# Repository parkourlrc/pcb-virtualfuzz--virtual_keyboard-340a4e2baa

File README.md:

# virtual_keyboard

Uses kmk for the firmware, maybe in the future I will switch to Rust.

The goal of this keyboard is to be one that I like, not one with a bunch
of fancy features. It's as minimal as I like it to be, 65% keyboards seem
good, but I still need F keys because for some games it better to have them.

For the arrow keys, I don't think it's that bad not having them thanks to
WASD keys.

## Schematic

## PCB

## Case

The case is supposed to stick together using screws, not sure if they will fit.\
I think I'll use some tape or a wire to hold it together if it doesn't fit.

## Bill of Materials

### Electronics

|QTY|Name|Part number|
|---|----|-----------|
|1|Orpheus PICO|
|81|Diodes|1N4148WL|
|81|Kailh Hotswap Sockets|

### Keyboard components

|QTY|Name|
|---|----|
|1|Bottom case|
|1|Top case|
|4|2mm (Self-drilling?) Screws|
|81|DSA keycaps|
|81|Cherry MX Switches|
|1|6u Stabilizer|
|2|2u Stabilizers|

## Keyboard Layout (KLE raw data)

ISO layout

Resize: Spacebar; Shift key
```
["Esc","F1","F2","F3","F4","F5","F6","F7","F8","F9","F10","F11","F12","Print screen","Delete"],
["#\n@","1\nà","2\né","3\nè","4\nê","5\n(","6\n)","7\n‘","8\n’","9\n«","0\n»","\"\n'","¨\n^",{w:2},"Backspace"],
[{w:1.5},"Tab","A","Z\n£","E\n€","R","T\n{","Y\n}","U","I","O","P","–\n-","±\n+",{x:0.25,w:1.25,h:2,w2:1.5,h2:1,x2:-0.25},"Enter"],
[{w:1.75},"Caps Lock","Q","S","D\n$","F","G","H","J","K","L","M","\\\n/","½\n*"],
[{w:1.25},"Shift",">\n<","W","X","C","V","B","N","?\n.","!\n,","…\n:","=\n;",{w:1.75},"Shift","↑"],
["Ctrl","Fn","Super","Alt",{a:7,w:6},"","Alt Gr","Super","Ctrl","←","↓","→"]
```

## License

[Licensed under the MIT license](LICENSE.md)

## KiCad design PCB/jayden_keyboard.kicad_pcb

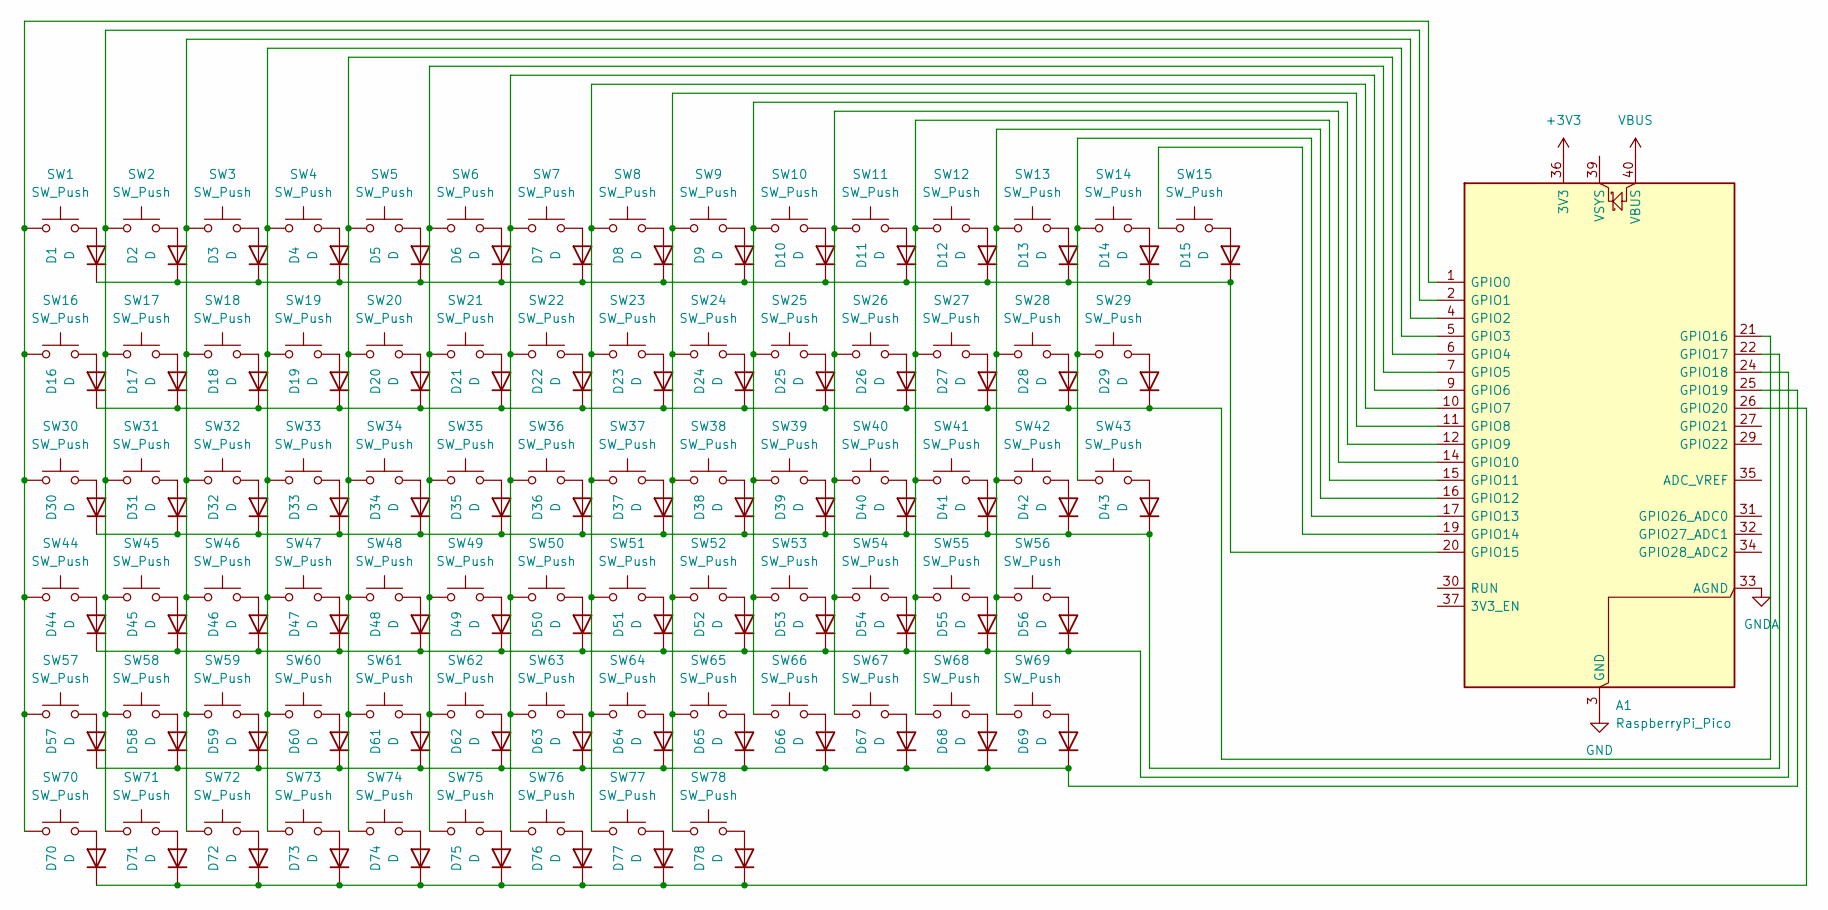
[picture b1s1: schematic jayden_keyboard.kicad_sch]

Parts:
A1: RaspberryPi_Pico; RaspberryPi_Pico_Common_THT_MountingHoles
D1, D2, D3, D4, D5, D6, D7, D8, D9, D10, D11, D12, D13, D14, D15, D16, D17, D18, D19, D20, D21, D22, D23, D24, D25, D26, D27, D28, D29, D30, D31, D32, D33, D34, D35, D36, D37, D38, D39, D40, D41, D42, D43, D44, D45, D46, D47, D48, D49, D50, D51, D52, D53, D54, D55, D56, D57, D58, D59, D60, D61, D62, D63, D64, D65, D66, D67, D68, D69, D70, D71, D72, D73, D74, D75, D76, D77, D78: D; D_DO-35_SOD27_P7.62mm_Horizontal
SW1, SW2, SW3, SW4, SW5, SW6, SW7, SW8, SW9, SW10, SW11, SW12, SW13, SW14, SW15, SW16, SW17, SW18, SW19, SW20, SW21, SW22, SW23, SW24, SW25, SW26, SW27, SW28, SW31, SW32, SW33, SW34, SW35, SW36, SW37, SW38, SW39, SW40, SW41, SW42, SW45, SW46, SW47, SW48, SW49, SW50, SW51, SW52, SW53, SW54, SW55, SW56, SW58, SW59, SW60, SW61, SW62, SW63, SW64, SW65, SW66, SW67, SW68, SW71, SW72, SW73, SW76, SW77: SW_Push; MX-Hotswap-1U
SW29: SW_Push; MX-Hotswap-2U
SW30: SW_Push; MX-Hotswap-1.5U
SW43: SW_Push; MX-Hotswap-ISO
SW44: SW_Push; MX-Hotswap-1.75U
SW57, SW70, SW75, SW78: SW_Push; MX-Hotswap-1.25U
SW69: SW_Push; MX-Hotswap-2.75U
SW74: SW_Push; MX-Hotswap-6.25U

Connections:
+3V3: A1.36 (3V3)
GND: A1.3 (GND), A1.8 (GND), A1.13 (GND), A1.18 (GND), A1.23 (GND), A1.28 (GND), A1.38 (GND)
GNDA: A1.33 (AGND)
unnamed: A1.1 (GPIO0), SW1.1, SW16.1, SW30.1, SW44.1, SW57.1, SW70.1
unnamed: A1.2 (GPIO1), SW2.1, SW17.1, SW31.1, SW45.1, SW58.1, SW71.1
unnamed: A1.4 (GPIO2), SW3.1, SW18.1, SW32.1, SW46.1, SW59.1, SW72.1
unnamed: A1.5 (GPIO3), SW4.1, SW19.1, SW33.1, SW47.1, SW60.1, SW73.1
unnamed: A1.6 (GPIO4), SW5.1, SW20.1, SW34.1, SW48.1, SW61.1, SW74.1
unnamed: A1.7 (GPIO5), SW6.1, SW21.1, SW35.1, SW49.1, SW62.1, SW75.1
unnamed: A1.9 (GPIO6), SW7.1, SW22.1, SW36.1, SW50.1, SW63.1, SW76.1
unnamed: A1.10 (GPIO7), SW8.1, SW23.1, SW37.1, SW51.1, SW64.1, SW77.1
unnamed: A1.11 (GPIO8), SW9.1, SW24.1, SW38.1, SW52.1, SW65.1, SW78.1
unnamed: A1.12 (GPIO9), SW10.1, SW25.1, SW39.1, SW53.1, SW66.1
unnamed: A1.14 (GPIO10), SW11.1, SW26.1, SW40.1, SW54.1, SW67.1
unnamed: A1.15 (GPIO11), SW12.1, SW27.1, SW41.1, SW55.1, SW68.1
unnamed: A1.16 (GPIO12), SW13.1, SW28.1, SW42.1, SW56.1, SW69.1
unnamed: A1.17 (GPIO13), SW14.1, SW29.1, SW43.1
unnamed: A1.19 (GPIO14), SW15.1
unnamed: A1.20 (GPIO15), D1.1 (K), D2.1 (K), D3.1 (K), D4.1 (K), D5.1 (K), D6.1 (K), D7.1 (K), D8.1 (K), D9.1 (K), D10.1 (K), D11.1 (K), D12.1 (K), D13.1 (K), D14.1 (K), D15.1 (K)
unnamed: A1.21 (GPIO16), D16.1 (K), D17.1 (K), D18.1 (K), D19.1 (K), D20.1 (K), D21.1 (K), D22.1 (K), D23.1 (K), D24.1 (K), D25.1 (K), D26.1 (K), D27.1 (K), D28.1 (K), D29.1 (K)
unnamed: A1.22 (GPIO17), D30.1 (K), D31.1 (K), D32.1 (K), D33.1 (K), D34.1 (K), D35.1 (K), D36.1 (K), D37.1 (K), D38.1 (K), D39.1 (K), D40.1 (K), D41.1 (K), D42.1 (K), D43.1 (K)
unnamed: A1.24 (GPIO18), D44.1 (K), D45.1 (K), D46.1 (K), D47.1 (K), D48.1 (K), D49.1 (K), D50.1 (K), D51.1 (K), D52.1 (K), D53.1 (K), D54.1 (K), D55.1 (K), D56.1 (K)
unnamed: A1.25 (GPIO19), D57.1 (K), D58.1 (K), D59.1 (K), D60.1 (K), D61.1 (K), D62.1 (K), D63.1 (K), D64.1 (K), D65.1 (K), D66.1 (K), D67.1 (K), D68.1 (K), D69.1 (K)
unnamed: A1.26 (GPIO20), D70.1 (K), D71.1 (K), D72.1 (K), D73.1 (K), D74.1 (K), D75.1 (K), D76.1 (K), D77.1 (K), D78.1 (K)
unnamed: D1.2 (A), SW1.2
unnamed: D2.2 (A), SW2.2
unnamed: D3.2 (A), SW3.2
unnamed: D4.2 (A), SW4.2
unnamed: D5.2 (A), SW5.2
unnamed: D6.2 (A), SW6.2
unnamed: D7.2 (A), SW7.2
unnamed: D8.2 (A), SW8.2
unnamed: D9.2 (A), SW9.2
unnamed: D10.2 (A), SW10.2
unnamed: D11.2 (A), SW11.2
unnamed: D12.2 (A), SW12.2
unnamed: D13.2 (A), SW13.2
unnamed: D14.2 (A), SW14.2
unnamed: D15.2 (A), SW15.2
unnamed: D16.2 (A), SW16.2
unnamed: D17.2 (A), SW17.2
unnamed: D18.2 (A), SW18.2
unnamed: D19.2 (A), SW19.2
unnamed: D20.2 (A), SW20.2
unnamed: D21.2 (A), SW21.2
unnamed: D22.2 (A), SW22.2
unnamed: D23.2 (A), SW23.2
unnamed: D24.2 (A), SW24.2
unnamed: D25.2 (A), SW25.2
unnamed: D26.2 (A), SW26.2
unnamed: D27.2 (A), SW27.2
unnamed: D28.2 (A), SW28.2
unnamed: D29.2 (A), SW29.2
unnamed: D30.2 (A), SW30.2
unnamed: D31.2 (A), SW31.2
unnamed: D32.2 (A), SW32.2
unnamed: D33.2 (A), SW33.2
unnamed: D34.2 (A), SW34.2
unnamed: D35.2 (A), SW35.2
unnamed: D36.2 (A), SW36.2
unnamed: D37.2 (A), SW37.2
unnamed: D38.2 (A), SW38.2
unnamed: D39.2 (A), SW39.2
unnamed: D40.2 (A), SW40.2
unnamed: D41.2 (A), SW41.2
unnamed: D42.2 (A), SW42.2
unnamed: D43.2 (A), SW43.2
unnamed: D44.2 (A), SW44.2
unnamed: D45.2 (A), SW45.2
unnamed: D46.2 (A), SW46.2
unnamed: D47.2 (A), SW47.2
unnamed: D48.2 (A), SW48.2
unnamed: D49.2 (A), SW49.2
unnamed: D50.2 (A), SW50.2
unnamed: D51.2 (A), SW51.2
unnamed: D52.2 (A), SW52.2
unnamed: D53.2 (A), SW53.2
unnamed: D54.2 (A), SW54.2
unnamed: D55.2 (A), SW55.2
unnamed: D56.2 (A), SW56.2
unnamed: D57.2 (A), SW57.2
unnamed: D58.2 (A), SW58.2
unnamed: D59.2 (A), SW59.2
unnamed: D60.2 (A), SW60.2
unnamed: D61.2 (A), SW61.2
unnamed: D62.2 (A), SW62.2
unnamed: D63.2 (A), SW63.2
unnamed: D64.2 (A), SW64.2
unnamed: D65.2 (A), SW65.2
unnamed: D66.2 (A), SW66.2
unnamed: D67.2 (A), SW67.2
unnamed: D68.2 (A), SW68.2
unnamed: D69.2 (A), SW69.2
unnamed: D70.2 (A), SW70.2
unnamed: D71.2 (A), SW71.2
unnamed: D72.2 (A), SW72.2
unnamed: D73.2 (A), SW73.2
unnamed: D74.2 (A), SW74.2
unnamed: D75.2 (A), SW75.2
unnamed: D76.2 (A), SW76.2
unnamed: D77.2 (A), SW77.2
unnamed: D78.2 (A), SW78.2
VBUS: A1.40 (VBUS)

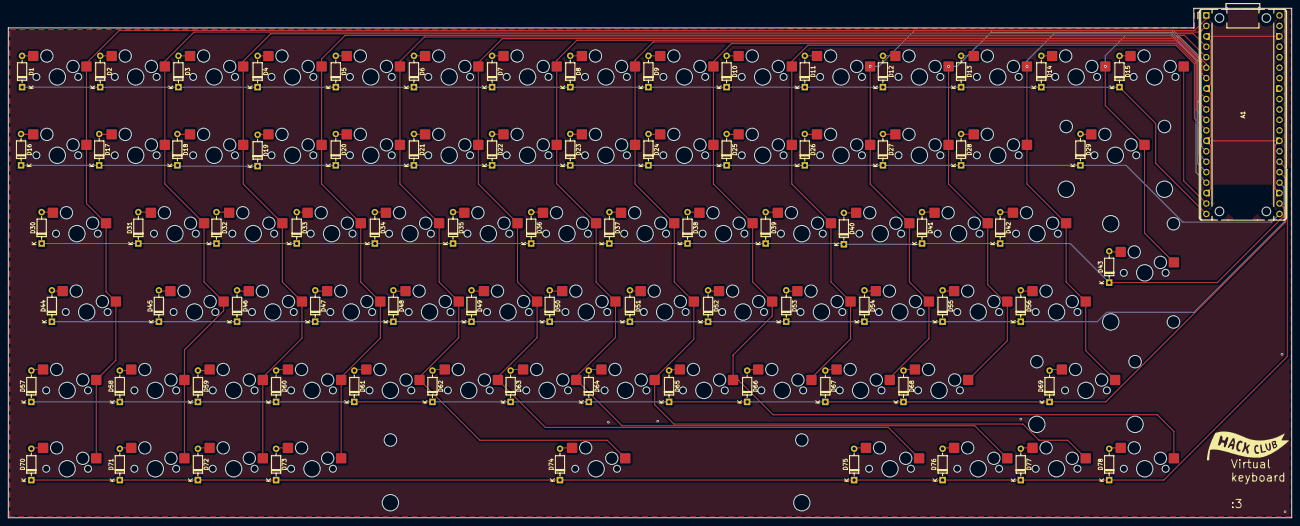
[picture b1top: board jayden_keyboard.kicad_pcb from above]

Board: 2 copper layers, 311.9 x 123.8 mm, 157 parts (0 on the bottom side), 100 nets.

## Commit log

2025-02-16 chore: Initial commit
    License project under MIT license.
2025-02-16 feat: Create kicad project and add pico
    The actual board is the orpheus pico
    https://orpheuspico.hackclub.com/docs/features
2025-03-02 feat: Add PCB layout
2025-03-02 feat: Update PCB and start working into the actual wiring
    Work on the keyboard layout.
2025-03-04 feat: Finish first potential PCB prototype
    Testing other layouts
2025-03-05 feat: Now an attempt with a new layout and choc v2
    Will try Cherry MX now.
2025-03-06 feat: Save before doing another change
2025-03-06 feat: Finished the PCB!
    Finally
2025-03-09 feat: Update PCB and add keyboard layout
2025-03-09 feat: Update CAD
    Maybe I'll work on this later...
2025-03-09 feat: Start writing the firmware and update keyboard layout
2025-03-09 feat: Have a barebones firmware
    Barebones but should work.
2025-03-12 feat: Add upper board
2025-03-13 feat: Make PCB use MX hotswaps
2025-03-15 feat: Finish PCB
    yipee
2025-03-15 feat: Update keyboard layout
2025-03-15 feat: Rename to arctic keyboard
2025-03-15 feat: Add ground fill
2025-03-15 feat: Add hackclub logo
2025-03-15 feat: FInish project layout
    Now into the readme
2025-03-16 feat: Work in progress readme
    Will be taking a break, I am DEFINITELY
    getting burned out, the deadline will be extended by at least
    a week.
2025-03-18 feat: Add BOM
2025-03-18 feat: Update readme with more screenshots
2025-03-20 feat: Rename keyboard
2025-03-22 feat: Update PCB to have arrow keys
2025-03-22 feat: Shorten TODO
    Remove irrelelvent things
2025-03-22 feat: Remove irrelevent part from README
    I was using this as a note
